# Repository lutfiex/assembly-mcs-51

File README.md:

# assembly-mcs-51
code project for mcs51 project

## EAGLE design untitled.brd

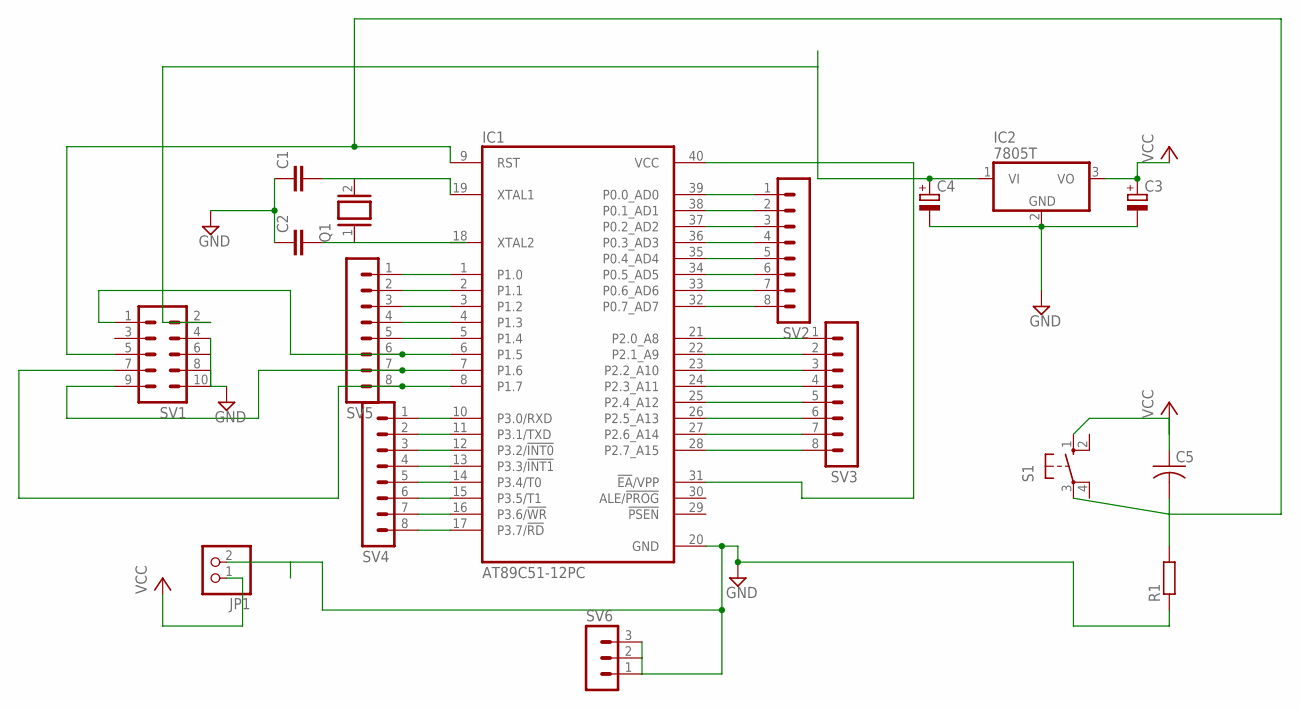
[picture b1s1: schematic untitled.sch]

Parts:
C1, C2: C2,5-3; C2.5-3
C3, C4: CPOL-EUB45181A; B45181A
C5: C-US025-024X044; C025-024X044
IC1: AT89C51-12PC; DIL40
IC2: 7805T; TO220H
JP1: PINHD-1X2; 1X02
Q1: XTAL/S; QS
R1: R0204/7; 0204/7
S1: 10-XX; B3F-10XX
SV1: MA05-2
SV2, SV3, SV4, SV5: MA08-1
SV6: MA03-1

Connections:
GND: C1.1, C2.1, C3.-, C4.-, IC1.20 (GND), IC2.2 (GND), JP1.2, R1.1, SV1.4, SV1.6, SV1.8, SV1.10, SV6.1, SV6.2, SV6.3
unnamed: IC1.6 (P1.5), SV1.1, SV5.6
unnamed: IC1.7 (P1.6), SV1.9, SV5.7
unnamed: IC1.8 (P1.7), SV1.7, SV5.8
unnamed: C1.2, IC1.19 (XTAL1), Q1.2
unnamed: C2.2, IC1.18 (XTAL2), Q1.1
unnamed: C4.+, IC1.31 (!EA!/VPP), IC1.40 (VCC), IC2.1 (VI), SV1.2
unnamed: IC1.10 (P3.0/RXD), SV4.1
unnamed: IC1.11 (P3.1/TXD), SV4.2
unnamed: IC1.12 (P3.2/!INT0), SV4.3
unnamed: IC1.13 (P3.3/!INT1), SV4.4
unnamed: IC1.14 (P3.4/T0), SV4.5
unnamed: IC1.15 (P3.5/T1), SV4.6
unnamed: IC1.16 (P3.6/!WR), SV4.7
unnamed: IC1.17 (P3.7/!RD), SV4.8
unnamed: IC1.1 (P1.0), SV5.1
unnamed: IC1.2 (P1.1), SV5.2
unnamed: IC1.3 (P1.2), SV5.3
unnamed: IC1.4 (P1.3), SV5.4
unnamed: IC1.5 (P1.4), SV5.5
unnamed: IC1.21 (P2.0_A8), SV3.1
unnamed: IC1.22 (P2.1_A9), SV3.2
unnamed: IC1.23 (P2.2_A10), SV3.3
unnamed: IC1.24 (P2.3_A11), SV3.4
unnamed: IC1.25 (P2.4_A12), SV3.5
unnamed: IC1.26 (P2.5_A13), SV3.6
unnamed: IC1.27 (P2.6_A14), SV3.7
unnamed: IC1.28 (P2.7_A15), SV3.8
unnamed: IC1.39 (P0.0_AD0), SV2.1
unnamed: IC1.38 (P0.1_AD1), SV2.2
unnamed: IC1.37 (P0.2_AD2), SV2.3
unnamed: IC1.36 (P0.3_AD3), SV2.4
unnamed: IC1.35 (P0.4_AD4), SV2.5
unnamed: IC1.34 (P0.5_AD5), SV2.6
unnamed: IC1.33 (P0.6_AD6), SV2.7
unnamed: IC1.32 (P0.7_AD7), SV2.8
unnamed: C5.2, IC1.9 (RST), R1.2, S1.3, SV1.5
VCC: C3.+, C5.1, IC2.3 (VO), JP1.1, S1.1 (S)

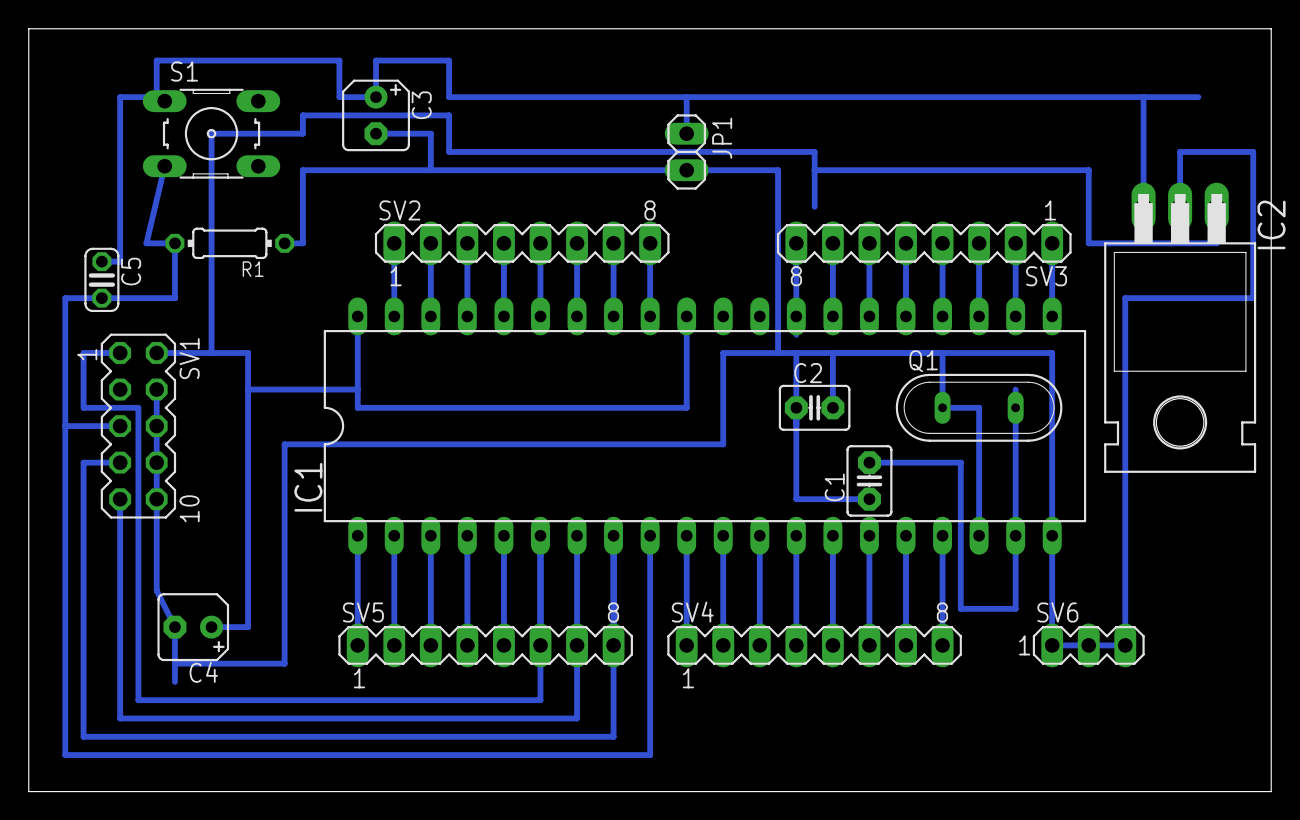
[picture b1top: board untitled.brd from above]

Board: 2 copper layers, 86.3 x 53.0 mm, 17 parts (0 on the bottom side), 38 nets.

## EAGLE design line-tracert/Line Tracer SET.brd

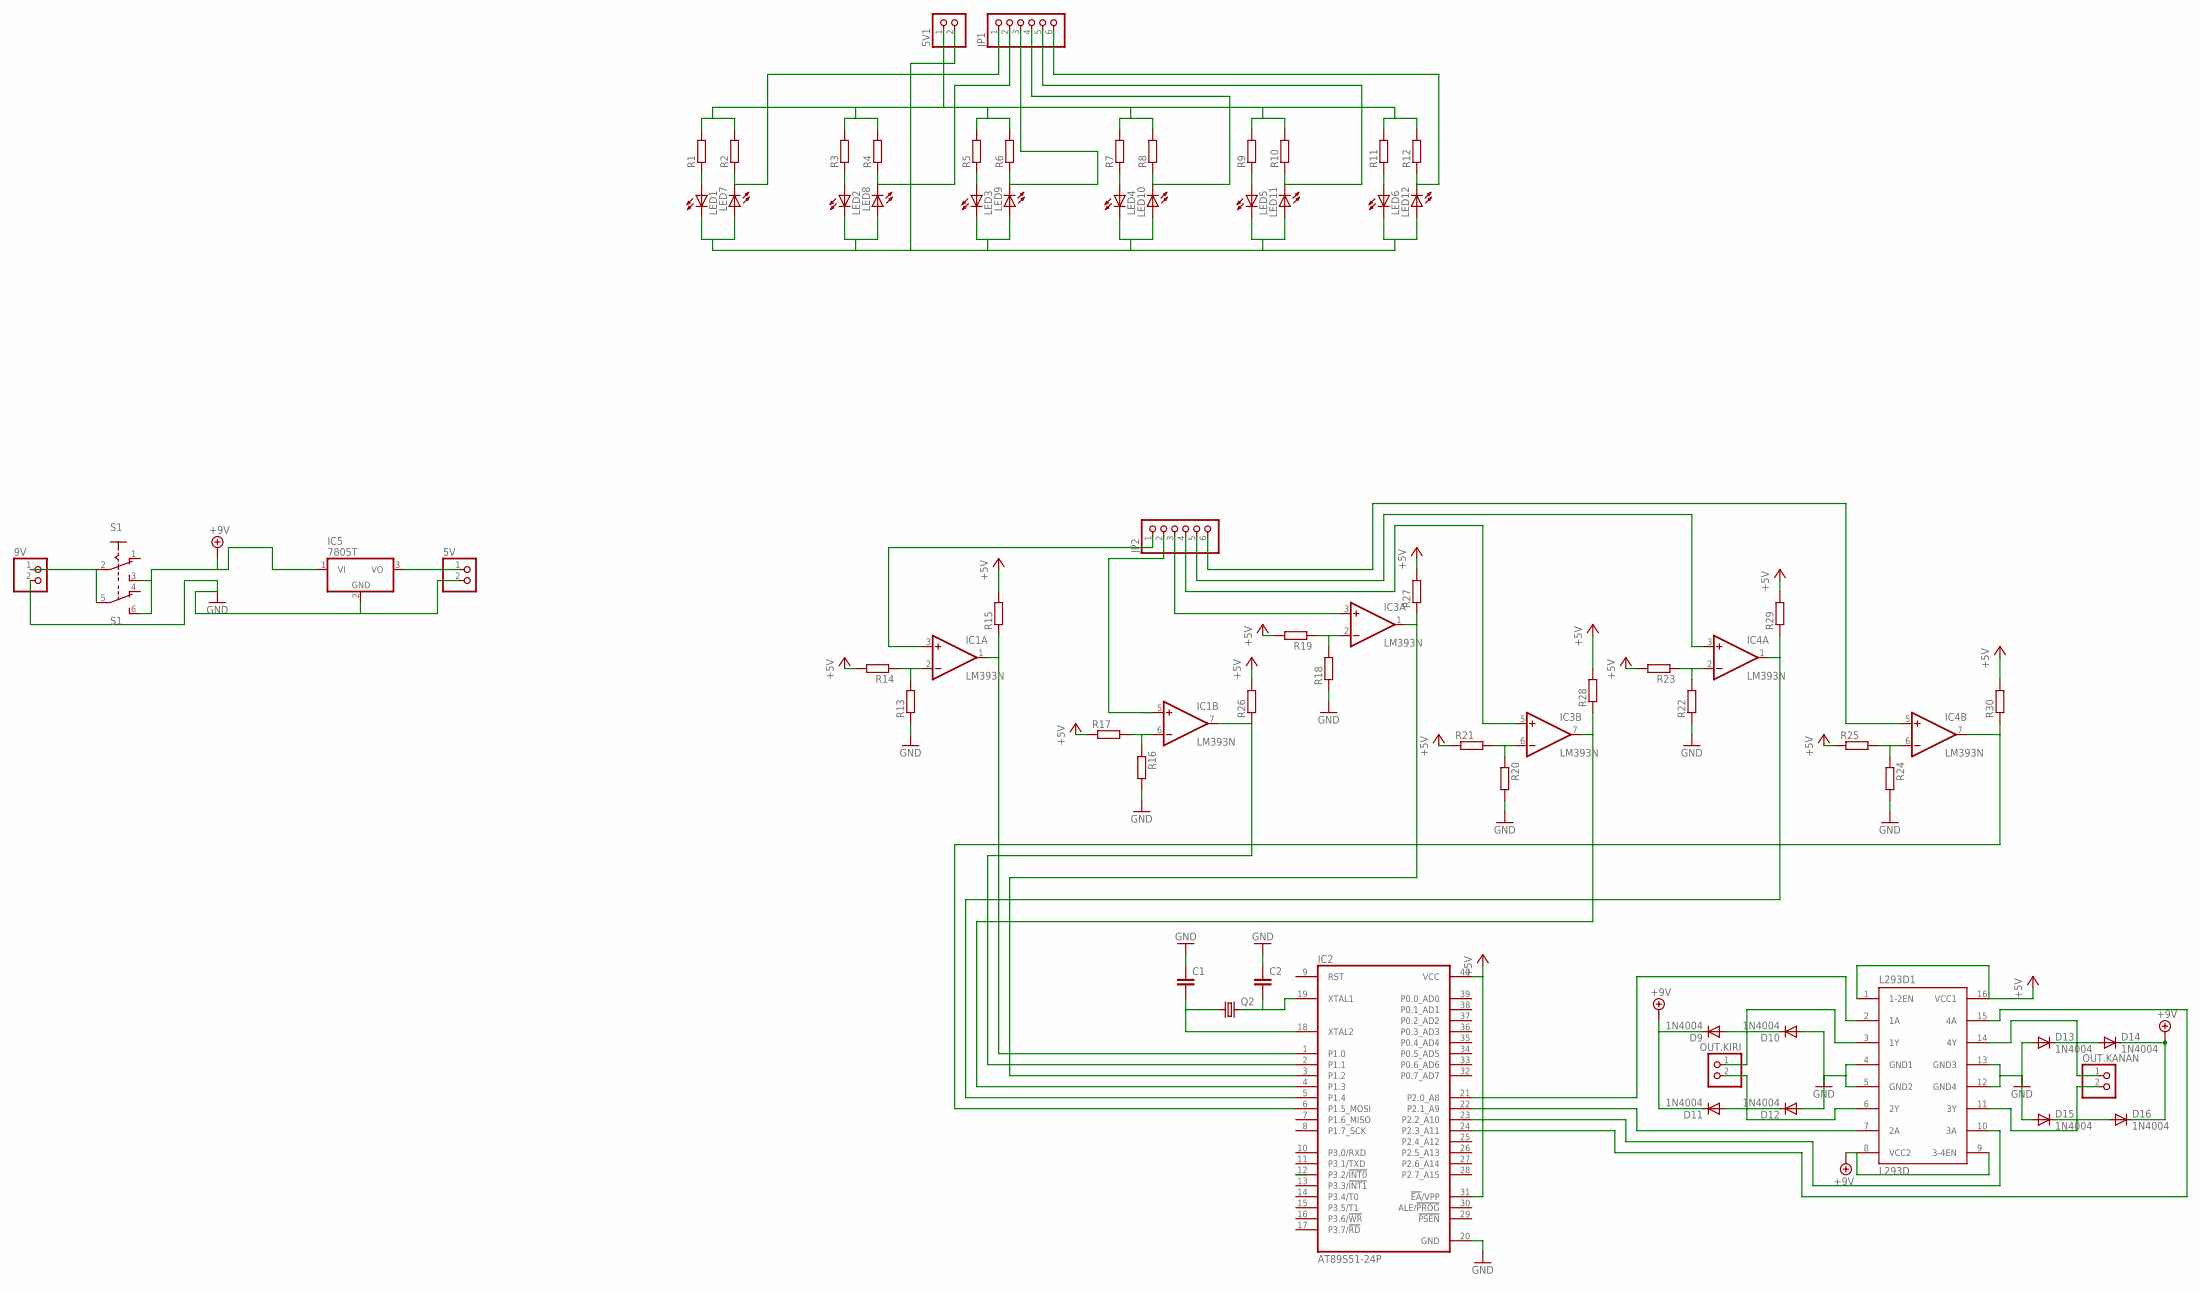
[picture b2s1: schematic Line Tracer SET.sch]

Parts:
5V, 5V1, 9V: PINHD-1X2; 1X02
C1, C2: C-EU025-024X044; C025-024X044
D9, D10, D11, D12, D13, D14, D15, D16: 1N4004; DO41-10
IC1, IC3, IC4: LM393N; DIL08
IC2: AT89S51-24P; DIL40
IC5: 7805T; TO220H
JP1, JP2: PINHD-1X6; 1X06
L293D1: L293D; DIL16
LED1, LED2, LED3, LED4, LED5, LED6, LED7, LED8, LED9, LED10, LED11, LED12: LED3MM
OUT.KANAN, OUT.KIRI: PINHD-1X2; 1X02
Q2: CRYSTALHC49S; HC49/S
R1, R2, R3, R4, R5, R6, R7, R8, R9, R10, R11, R12, R13, R14, R15, R16, R17, R18, R19, R20, R21, R22, R23, R24, R25, R26, R27, R28, R29, R30: R-EU_0207/10; 0207/10
S1: A68-A31

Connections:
5V: 5V1.1, R1.2, R2.2, R3.2, R4.2, R5.2, R6.2, R7.2, R8.2, R9.2, R10.2, R11.2, R12.2
+5V: IC2.31 (!EA!/VPP), IC2.40 (VCC), L293D1.1 (1-2EN), L293D1.16 (VCC1), R14.2, R15.2, R17.1, R19.2, R21.1, R23.2, R25.1, R26.2, R27.2, R28.2, R29.2, R30.2
+9V: D9.C, D11.C, D14.C, D16.C, IC5.1 (VI), L293D1.8 (VCC2), L293D1.9 (3-4EN), S1.3 (S), S1.6 (S)
GND: 5V.2, 9V.2, C1.1, C2.1, D10.A, D12.A, D13.A, D15.A, IC2.20 (GND), IC5.2 (GND), L293D1.4 (GND1), L293D1.5 (GND2), L293D1.12 (GND4), L293D1.13 (GND3), R13.1, R16.2, R18.1, R20.2, R22.1, R24.2
GNDS: 5V1.2, LED1.K (C), LED2.K (C), LED3.K (C), LED4.K (C), LED5.K (C), LED6.K (C), LED7.A, LED8.A, LED9.A, LED10.A, LED11.A, LED12.A
unnamed: IC3.3 (+IN), JP2.3
unnamed: LED3.A, R5.1
unnamed: IC1.2 (-IN), R13.2, R14.1
unnamed: LED4.A, R7.1
unnamed: IC3.5 (+IN), JP2.4
unnamed: LED5.A, R9.1
unnamed: JP1.5, LED11.K (C), R10.1
unnamed: LED6.A, R11.1
unnamed: IC4.5 (+IN), JP2.6
unnamed: LED1.A, R1.1
unnamed: JP1.2, LED8.K (C), R4.1
unnamed: LED2.A, R3.1
unnamed: IC1.6 (-IN), R16.1, R17.2
unnamed: C2.2, IC2.19 (XTAL1), Q2.2
unnamed: JP1.3, LED9.K (C), R6.1
unnamed: C1.2, IC2.18 (XTAL2), Q2.1
unnamed: IC3.2 (-IN), R18.2, R19.1
unnamed: IC3.6 (-IN), R20.1, R21.2
unnamed: IC4.2 (-IN), R22.2, R23.1
unnamed: IC4.6 (-IN), R24.1, R25.2
unnamed: IC2.21 (P2.0_A8), L293D1.2 (1A)
unnamed: D11.A, D12.C, L293D1.6 (2Y), OUT.KIRI.2
unnamed: IC2.3 (P1.2), IC3.1 (OUT), R27.1
unnamed: D15.C, D16.A, L293D1.11 (3Y), OUT.KANAN.2
unnamed: D13.C, D14.A, L293D1.14 (4Y), OUT.KANAN.1
unnamed: IC2.22 (P2.1_A9), L293D1.7 (2A)
unnamed: IC2.23 (P2.2_A10), L293D1.10 (3A)
unnamed: IC2.24 (P2.3_A11), L293D1.15 (4A)
unnamed: IC1.1 (OUT), IC2.1 (P1.0), R15.1
unnamed: D9.A, D10.C, L293D1.3 (1Y), OUT.KIRI.1
unnamed: IC2.5 (P1.4), IC4.1 (OUT), R29.1
unnamed: IC2.4 (P1.3), IC3.7 (OUT), R28.1
unnamed: IC2.6 (P1.5_MOSI), IC4.7 (OUT), R30.1
unnamed: IC1.7 (OUT), IC2.2 (P1.1), R26.1
unnamed: JP1.1, LED7.K (C), R2.1
unnamed: IC1.5 (+IN), JP2.2
unnamed: JP1.4, LED10.K (C), R8.1
unnamed: IC4.3 (+IN), JP2.5
unnamed: JP1.6, LED12.K (C), R12.1
unnamed: 5V.1, IC5.3 (VO)
unnamed: 9V.1, S1.2, S1.5
unnamed: IC1.3 (+IN), JP2.1
V+: IC1.8 (V+), IC3.8 (V+), IC4.8 (V+)
V-: IC1.4 (V-), IC3.4 (V-), IC4.4 (V-)

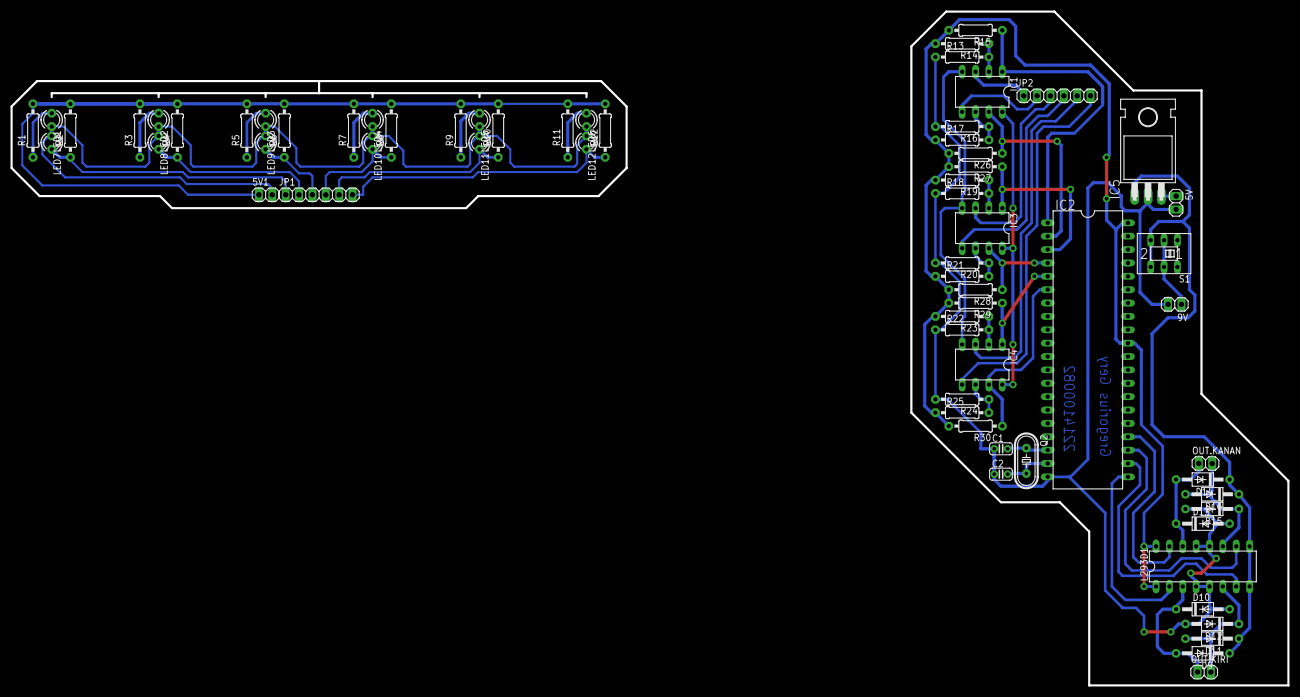
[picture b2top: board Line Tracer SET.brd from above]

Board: 2 copper layers, 242.6 x 128.0 mm, 67 parts (0 on the bottom side), 49 nets.

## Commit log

2020-04-24 water tank
2020-04-24 Create water-tank
2020-04-24 Add files via upload
    water tank for mcs51 with assembly language
2020-04-24 readme.txt
    line tracert robot with mcs 51
